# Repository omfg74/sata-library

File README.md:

# sata-library

Полка, в которой диски 3.5" лежат на местах. Ярус — четыре диска и высота 1U. Два яруса — 8 дисков, третий ставится теми же деталями. Одновременно под 12 В только одна сата-плата, и на ней моторы раскручиваются по одному.

Контроллер — ESP32. Он включает питание. Байты архива через ESP32 не идут: у него нет SATA, а USB слишком медленный для диска. Архив принимает Raspberry Pi 4 или мини-ПК и пишет его через покупные мосты USB–SATA командой `rsync`. Договор разъёмов — [hardware/INTERFACE.md](hardware/INTERFACE.md).

| что | чем открыть |
| --- | --- |
| схема и плата | KiCad 8, проекты в `hardware/controller` и `hardware/sata-board` |
| корпус | OpenSCAD, файлы в `cad/stack`. Картинка двух ярусов ниже |
| печать | PrusaSlicer, Cura или OrcaSlicer, STL из OpenSCAD |
| прошивка | VS Code с PlatformIO или Arduino IDE, каталог `hardware/controller/firmware` |

Платы заказывать нельзя. Зоны земли не залиты, DRC не прогнан, на сата-плате входной IRF4905 и стабилитрон D1 разведены неверно. Смотреть файлы: `flatpak run org.kicad.KiCad` (KiCad 10; файлы записаны как KiCad 8, сохранение поднимает формат). Футпринт XT60 на контроллере — заглушка, его подгоняют под разъём в руках.

Наборный ярус описан в [cad/stack/README.md](cad/stack/README.md). Порядок включения — в [docs/banks.md](docs/banks.md). Что ещё не закрыто без детали в руках — в [docs/open-questions.md](docs/open-questions.md).

Ниже отдельно лежит первая стойка на один юнит и примерка одного отсека. Наборный ярус их файлы не переписывает: `cad/rack.scad`, `cad/bay.scad`.

## С чего печатать ярус

```bash
make stl
```

Нужен OpenSCAD. В `cad/out/` появятся STL примерки и яруса. Ярус — файлы `stack-*.stl`.

PETG, сопло 0.4 мм, слой 0.2 мм, три стенки. Сколько каких деталей и какой длины трубки — в [cad/stack/README.md](cad/stack/README.md). Длинные пролёты не печатаются: это трубки 6 мм. Печатная деталь влезает в 170 мм.

## Софт

Хост включает слот и один диск, сверяет серийник и вызывает `rsync`. Паузу между раскрутками (`spin_pause_s`, в примере 8 с) держит хост. Сухой прогон на плату не выходит и `rsync` не запускает.

```bash
make test
PYTHONPATH=src python3 -m sata_library backup \
  --config config/library.example.toml --slot 1 --disk 1 --source /data --dry-run
```

В примере серийник `REPLACE-ME`, и сухой прогон подставляет его же. Это не чтение полки. Пока в манифесте пустая строка, копирование запрещено: сначала `identify`, потом серийник руками в TOML.

Живой контроллер:

```bash
PYTHONPATH=src python3 -m sata_library backup \
  --config config/library.toml --slot 1 --disk 1 --source /data --port /dev/ttyUSB0
```

Без `--port` команда останавливается с `not_connected`. Порт — 115200 8N1, строки из [docs/controller.md](docs/controller.md). `path_contains` на живом запуске обязателен. `mount` — уже смонтированный каталог диска, туда пишет `rsync -a`.

Диски разбираются из `lsblk -J`. У моста USB–SATA поле `tran` часто `usb`, поэтому полка фильтруется строкой `path_contains`, а не типом шины.

## Первая примерка и стойка 1U

Калибр и салазки — от варианта с подвижным разъёмом. Боевая полка их не использует.

`gauge.stl` — короткий ложемент, если снова мерить, где на корпусе сидит разъём. Диск кладётся к левому борту и на пол, задней плоскостью к нулю линеек. Окно в `sled.scad` сейчас по центру пластины и размером разъёма не является. Питание на эту примерку не подавать.

Каркас на один юнит — четыре уголка и восемь трубок, корзина на каждый диск.

`corner.stl` содержит левый и правый уголок. Печатать файл дважды. Гнездо 8.4 мм принимает трубку от 4 до 8 мм. В сборке по умолчанию трубка 6 мм: между верхней и нижней остаётся 29 мм, из них 1.6 мм пол корзины и 26.1 мм диск. Число корзин и диаметр задаются в `cad/params.scad`. Подробности в [docs/rack.md](docs/rack.md).

## Документы

- [docs/concept.md](docs/concept.md) — роли хоста и контроллера
- [docs/banks.md](docs/banks.md) — включение слота и одного диска
- [docs/controller.md](docs/controller.md) — текстовый протокол
- [docs/rack.md](docs/rack.md) — каркас 1U из уголков и трубок
- [docs/mechanics.md](docs/mechanics.md) — первая примерка подвижного разъёма
- [docs/hardware.md](docs/hardware.md) — из чего собрать: хост ARM, SATA или USB, питание и каркас
- [docs/open-questions.md](docs/open-questions.md) — что решить дальше
- [hardware/INTERFACE.md](hardware/INTERFACE.md) — разъёмы, питание, I2C

Лицензия MIT.

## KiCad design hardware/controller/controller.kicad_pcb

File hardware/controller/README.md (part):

# Плата контроллера полки

Плата включает 12 В на один слот и по I2C крутит диски на плате SATA. Байты архива через неё не идут: хост → USB 3.0 → покупной хаб → мост на плате SATA. На этой плате нет пар USB, пар SATA, W5500 и разъёма Ethernet.

Контроллер молчит, пока хост не пришлёт строку. Протокол — `hardware/INTERFACE.md`: `PING`, `ESTOP`, `STATE`, `SLOT n ON/OFF`, `DISK n d ON/OFF`, 115200 8N1. Паузу около 8 с между раскрутками дисков держит хост, в прошивке таймера на это нет.

## Открыть в KiCad

KiCad 8, бесплатный: https://www.kicad.org/

File → Open Project → `hardware/controller/controller.kicad_pro`.

Символы и футпринты лежат в `libs/` этого каталога (`sym-lib-table` и `fp-lib-table` смотрят на `${KIPRJMOD}`). Системная библиотека KiCad не нужна. Файлы собирает `python3 gen_board.py` из этого каталога; править плату лучше там и пересобрать.

## Что на плате

Вход XT60, ключ от переполюсовки IRF4905, предохранитель 10 А, всегда включённые 12 В. Модуль LM2596 (покупной, на гребёнке 1x4: VIN, GND, VOUT, GND) делает 5 В. AMS1117-3.3 делает 3,3 В для ESP32-WROOM-32E. Свой импульсный стабилизатор на плате не разведён.

Четыре одинаковых слота. На каждом полифуз 5 А и IRF4905 верхним ключом: исток на предохранителе, сток на клемму, затвор подтянут к истоку 100 кОм. Без прошивки слот выключен. 2N7002 тянет затвор к земле, когда GPIO высокий. Земля общая с USB и дисками, нижнего ключа нет.

Клемма 5,08 мм: контакт 1 — квадрат, шёлк «+», это +12V слота. Контакт 2 — шёлк «−», земля. К плате SATA — 18 AWG, короче 30 см, без диода в разрыв.

Гребёнка 2x5, шаг 2,54, вилка. Контакт 1 — квадрат и треугольник «1». Нумерация IDC: 1 и 2 в ряду торца, дальше по длинной стороне пары 3/4, 5/6, 7/8, 9/10. На плате торец (1, 2) ближе к верху, длинная сторона идёт вниз. Кабель прямой, контакт 1 к контакту 1, без переворота.

| Контакт | Сигнал |
| --- | --- |
| 1 | 3V3_AUX, всегда есть, не больше 50 мА |
| 2 | GND |
| 3 | PRESENT_N, плата SATA замыкает на землю |
| 4 | GND |
| 5 | SDA этого слота |
| 6 | SCL этого слота |
| 7 | GND |
| 8 | NC |
| 9 | NC |
| 10 | GND |

Подтяжек I2C на этих гребёнках нет: они стоят на плате SATA. На корневой шине, до мультиплексора, одна пара 4,7 кОм к 3,3 В.

TCA9548A, адрес 0x70 (A0 A1 A2 на земле). Канал 0 — слот 1, канал 3 — слот 4. SDA/SCL канала идут только на контакты 5 и 6 своей гребёнки. Сброс — GPIO13, активный низ, 10 кОм к 3,3 В.

PCF8574 на корневой шине, адрес 0x20, выводы никуда не идут. Это запас. Дисковый PCA9554 с тем же адресом 0x20 сидит за мультиплексором, на корне его нет.

ESP32-WROOM-32E антенной к верхней кромке. Под антенной медь не разведена, на обоих слоях зона запрета. GPIO слотов: 25, 26, 27, 14. PRESENT: 34, 35, 36, 39, с внешней подтяжкой 10 кОм к 3,3 В. I2C: GPIO21 SDA, GPIO22 SCL. Светодиод сердцебиения: GPIO32 через 1 кОм. EN и IO0 подтянуты к 3,3 В по 10 кОм, кнопки на землю.

Гребёнка UART 1x6, подпись UART: 3V3, GND, TX (GPIO1), RX (GPIO3), EN, IO0.

Плата ровно 100,0 × 100,0 мм, 1,6 мм, два слоя. Отверстия M3, сверло 3,2 мм: (4, 4), (96, 4), (4, 96), (96, 96). Клеммы слотов по нижнему краю, слева направо SLOT1…SLOT4, гребёнка сигнала рядом со своей клеммой. Корпуса TO-220 лежат плашмя, в дворе. Зоны земли на F.Cu и B.Cu нарисованы, но не залиты: в KiCad нажать B, потом DRC.

## BOM

Количества и футпринты — в `BOM.csv`. Ниже — что покупать и зачем.

| Кол-во | Деталь | Зачем |
| --- | --- | --- |
| 1 | ESP32-WROOM-32E | Модуль с антенной на плате. Голый кристалл и отдельная антенна тут не нужны. |
| 5 | IRF4905, TO-220 | P-канал, верхний ключ. Один на входе, четыре на слоты. Выводы 1=G, 2=D, 3=S. |
| 4 | 2N7002, SOT-23 | Тянет затвор IRF4905 к земле. Выводы этой разводки: 1=G, 2=S, 3=D. У части лотов порядок другой — сверить с даташитом пакета. |
| 1 | AMS1117-3.3, SOT-223 | 5 В → 3,3 В. Выводы 1=GND, 2=VOUT, 3=VIN, вкладка = VOUT. |
| 1 | TCA9548A, TSSOP-24 | Мультиплексор I2C, адрес 0x70. |
| 1 | PCF8574, SOIC-16 | Запас на корневой шине, адрес 0x20. Можно не паять. |
| 1 | Предохранитель 10 А, 5×20 мм, и держатель | После ключа переполюсовки. Шаг держателя на плате 22 мм — сверить с деталью. |
| 4 | Полифуз 2920, удержание около 5 А | На каждый слот, до силового ключа. |
| 4 | Клемма винтовая 2 контакта, шаг 5,08 мм | Питание слота. Низкий корпус, чтобы уложиться в 10 мм. |
| 4 | Вилка 2×5, шаг 2,54 мм | IDC к плате SATA. Контакт 1 — квадрат. |
| 1 | Модуль LM2596, 12 В → 5 В | Покупной. На плату выведена только гребёнка. Свой дроссель не разведён. |
| 1 | XT60, розетка на плату | Вход 12 В. Футпринт на плате — заглушка. |
| 1 | Стабилитрон 15 В, SOD-123 | Затвор-исток входного IRF4905. Катод (полоска, контакт 1) к истоку. |
| 1 | Адаптер USB-UART 3,3 В | Только для прошивки, на гребёнку UART. |

Остальное — 0805: 10 мкФ на входе и выходе AMS1117 и у ESP32, 100 нФ у ESP32 и у микросхем, 4,7 кОм на корневой I2C, 10 кОм на EN, IO0, сброс TCA и PRESENT, 100 кОм на затворах, 1 кОм на светодиод и на затворы 2N7002.

## Прошивка

Каталог `firmware/`. PlatformIO: плата `esp32dev`, framework Arduino, монитор 115200. Либо Arduino IDE, та же плата.

`pio run` из `firmware/` собирает образ для `esp32dev`. На плату его отсюда не заливали: ESP32 не был подключён. Правила слотов отдельно гоняются на хосте, без Arduino:

```
g++ -std=c++17 -Wall -Wextra -I firmware/src -o /tmp/policy_test firmware/policy_test.cpp firmware/src/policy.cpp && /tmp/policy_test
```

Правила «один слот», «DISK при выключенном слоте не меняет состояние», «ESTOP гасит всё», «n вне 1…4 — ошибка» лежат в `firmware/src/policy.cpp`, без Arduino.

Заливка, когда есть адаптер:

1. Адаптер USB-UART 3,3 В на гребёнку UART: 3V3, GND, TX адаптера на RX платы (GPIO3), RX адаптера на TX платы (GPIO1).
2. Зажать кнопку IO0 (или замкнуть IO0 на землю), нажать EN, отпустить IO0.
3. `pio run -t upload` из `firmware/`. Монитор — 115200. Плата сама ничего не печатает, пока не придёт строка.

Wi-Fi выключен, пока нет `firmware/include/secrets.h`. В репозитории только `secrets.h.example` с `WIFI_ENABLED 0`. Пароль в репозиторий не класть. Даже с Wi-Fi это те же короткие команды, порт 2323, без передачи архива.

Перед `SLOT n ON` прошивка смотрит PRESENT. Если нога высокая — `ERR not_present`, 12 В не включается. После включения ждёт до 300 мс и читает AT24C02 0x50 на канале `n-1`. Первые байты должны быть `S L I B`. Иначе слот снова гаснет: `ERR no_eeprom` или `ERR i2c`. PCA9554 0x20 на том же канале перед первым диском настраивается выходами в ноль: после питания он весь вход.

## Провод к одной плате SATA

Клемма: 18 AWG, плюс на контакт 1 (квадрат, «+»), минус на контакт 2 («−»). Короче 30 см. Диод в этот провод не ставить.

Шлейф IDC 2×5, прямой, контакт 1 к контакту 1. Треугольник на этой плате смотрит на тот же конец, что и квадрат на плате SATA. 3,3 В на контакте 1 — вспомогательное, его не коммутирует ключ слота. PRESENT_N плата SATA сажает на землю, когда она на месте.

Оранжевый провод 3,3 В питания SATA сюда не подключать. VBUS кабеля USB с хоста на эту плату не подавать: земля общая, питание 5 В дисков идёт своим путём на плате SATA.

## Перед заказом платы

- Футпринт XT60 — заглушка: площадки 5 мм, шаг 7,1 мм, шёлк «XT60 +12V» и «MATCH PART». Подогнать под ту розетку, которая в руках. На схеме та же заметка.
- Прижать IRF4905 к плате и измерить высоту. Бюджет корпуса — 10 мм. Плашмя корпус около 4,6 мм, но изогнутые выводы могут вылезти. Клеммы брать низкие. Модуль LM2596, если надеть его на гребёнку стоймя, в 10 мм не влезет: поставить рядом и припаять проводами.
- USB на эту плату не разводить. Данные — покупной хаб. На шелкографии так и написано.
- Шаг держателя предохранителя 5×20 сверить с деталью (на плате 22 мм).
- У 2N7002 сверить порядок ног с лотом: здесь 1=G, 2=S, 3=D.
- В KiCad нажать B, чтобы залить землю, затем Inspect → Design Rules Checker. Заливки в файле нет, DRC не запускался. KiCad 10 стоит через Flatpak, файлы записаны как KiCad 8, сохранение поднимает формат.

## Чего файл платы не гарантирует

DRC не запускался. Плату нельзя считать готовой к производству, пока зоны не залиты и DRC в KiCad не пройден. KiCad 10 стоит через Flatpak. Сохранение из него поднимает формат файлов с KiCad 8.

Дорожки 12 В слотов и вход до предохранителя — 2 мм. Возврат земли слота — 1,5 мм. Ветки затвора и стабилитрона — 0,4 мм, по ним не идёт ток слота. Переход 12 В с нижнего слоя на верхний — четыре отверстия сверлом 0,6 мм в ряд вдоль дорожки, шаг 1,6 мм. Площадки 1,2 мм лежат внутри дорожки 2 мм. Пара отверстий на пике 3–4 А яруса была на пределе, четыре делят тот же ток.

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
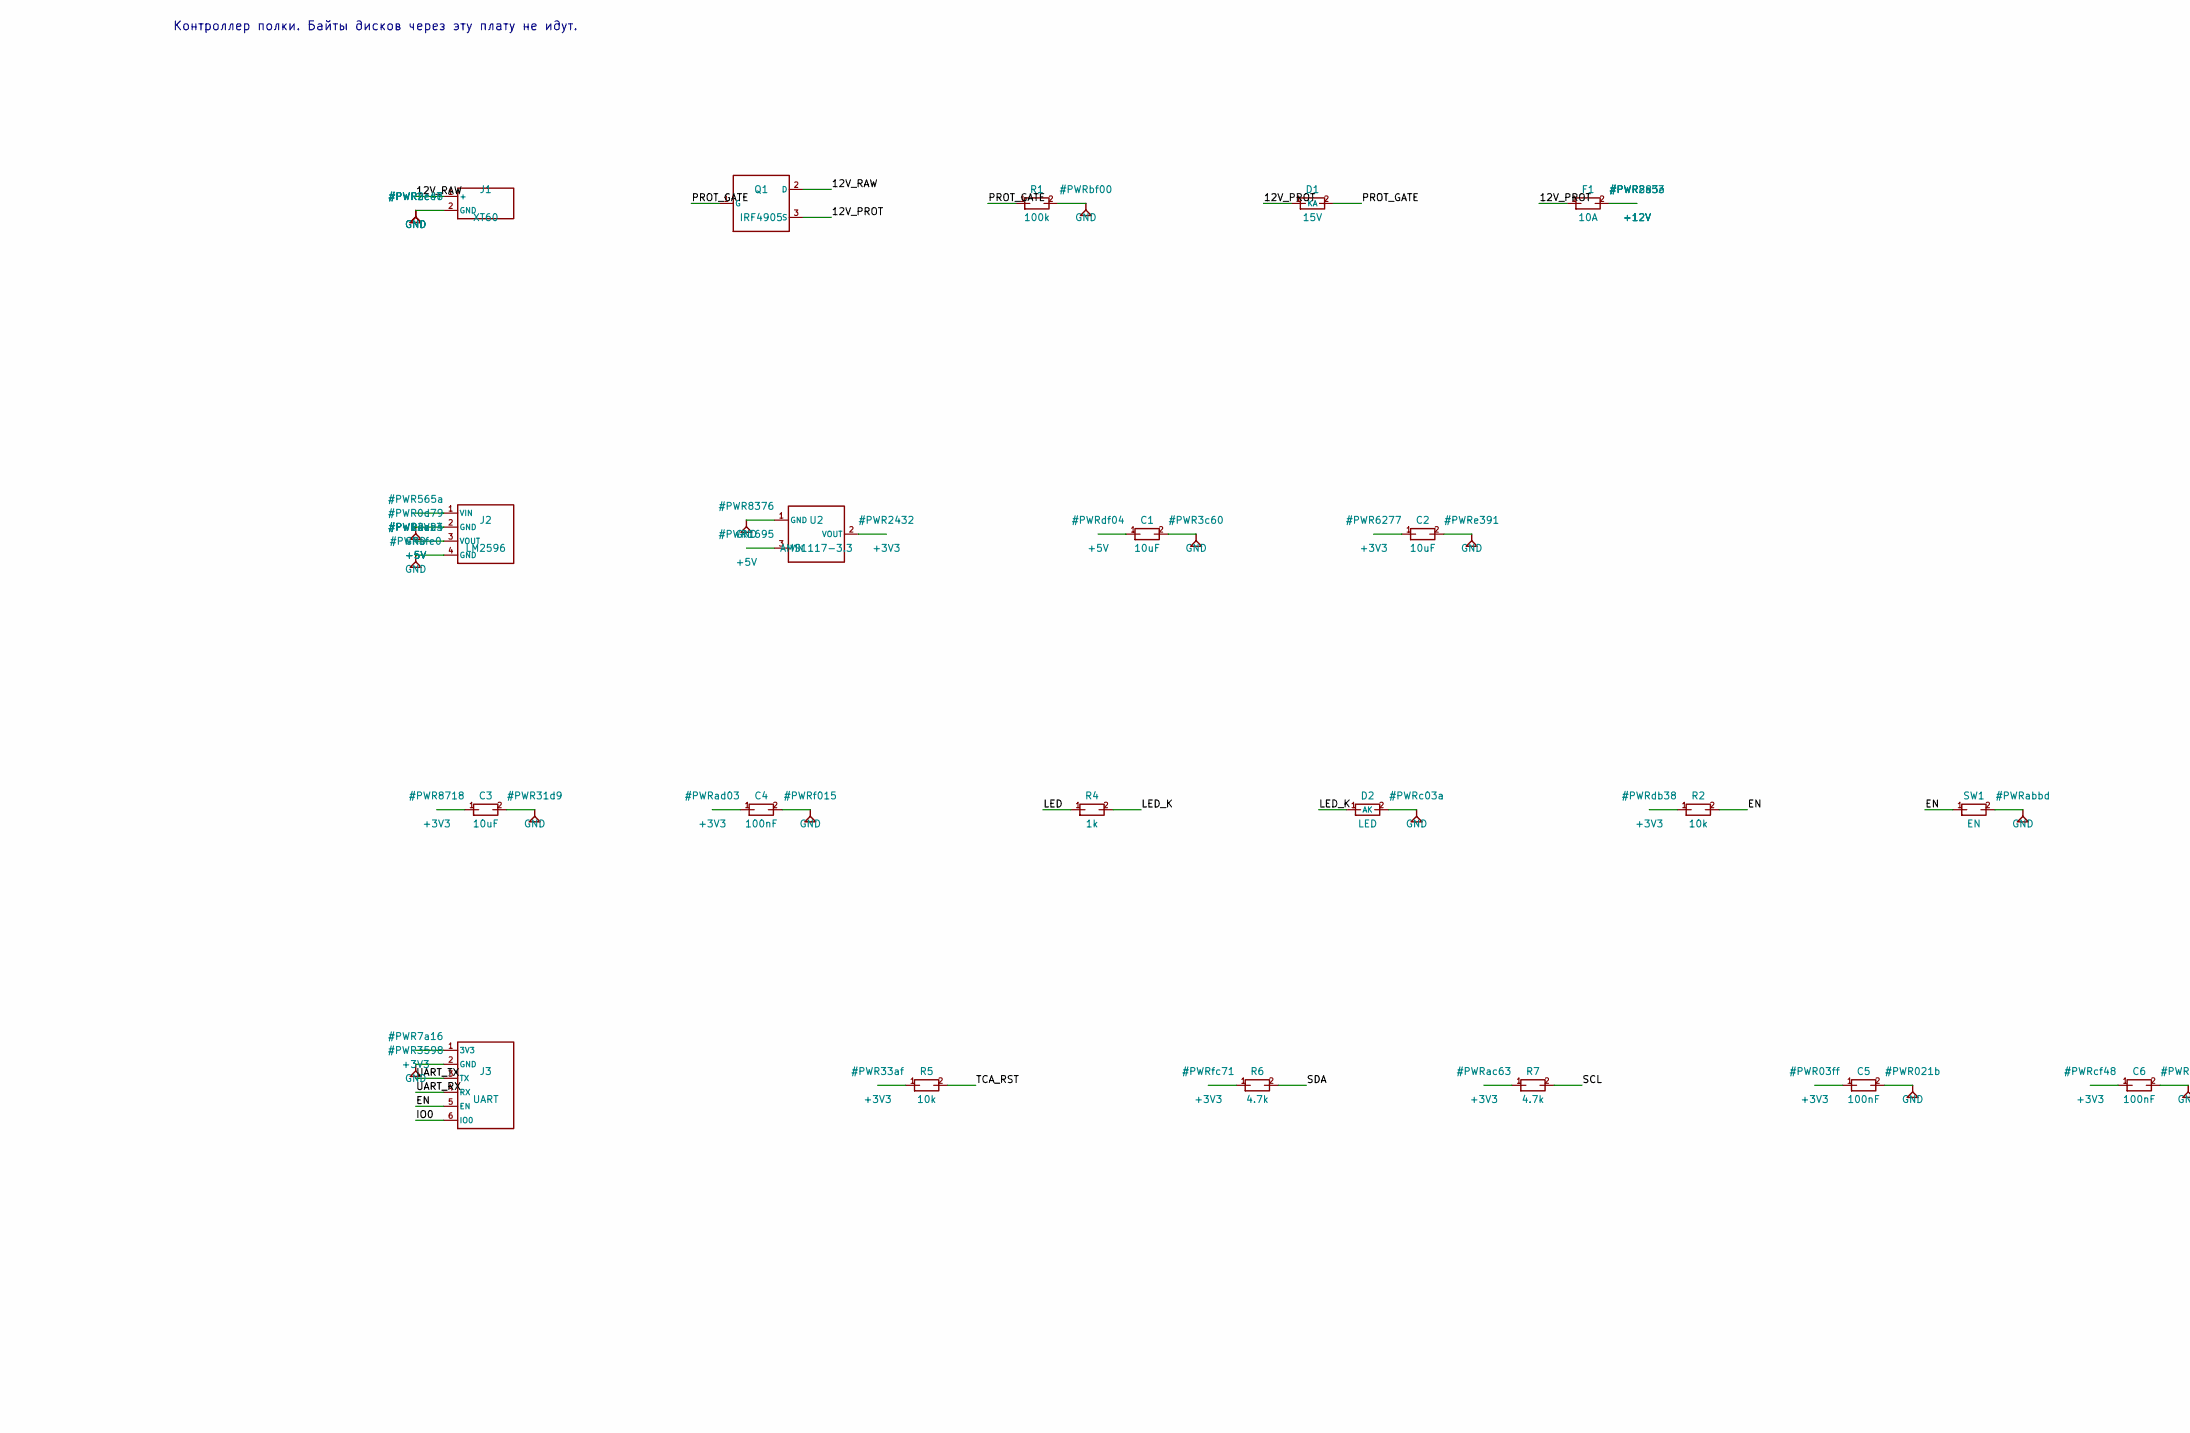
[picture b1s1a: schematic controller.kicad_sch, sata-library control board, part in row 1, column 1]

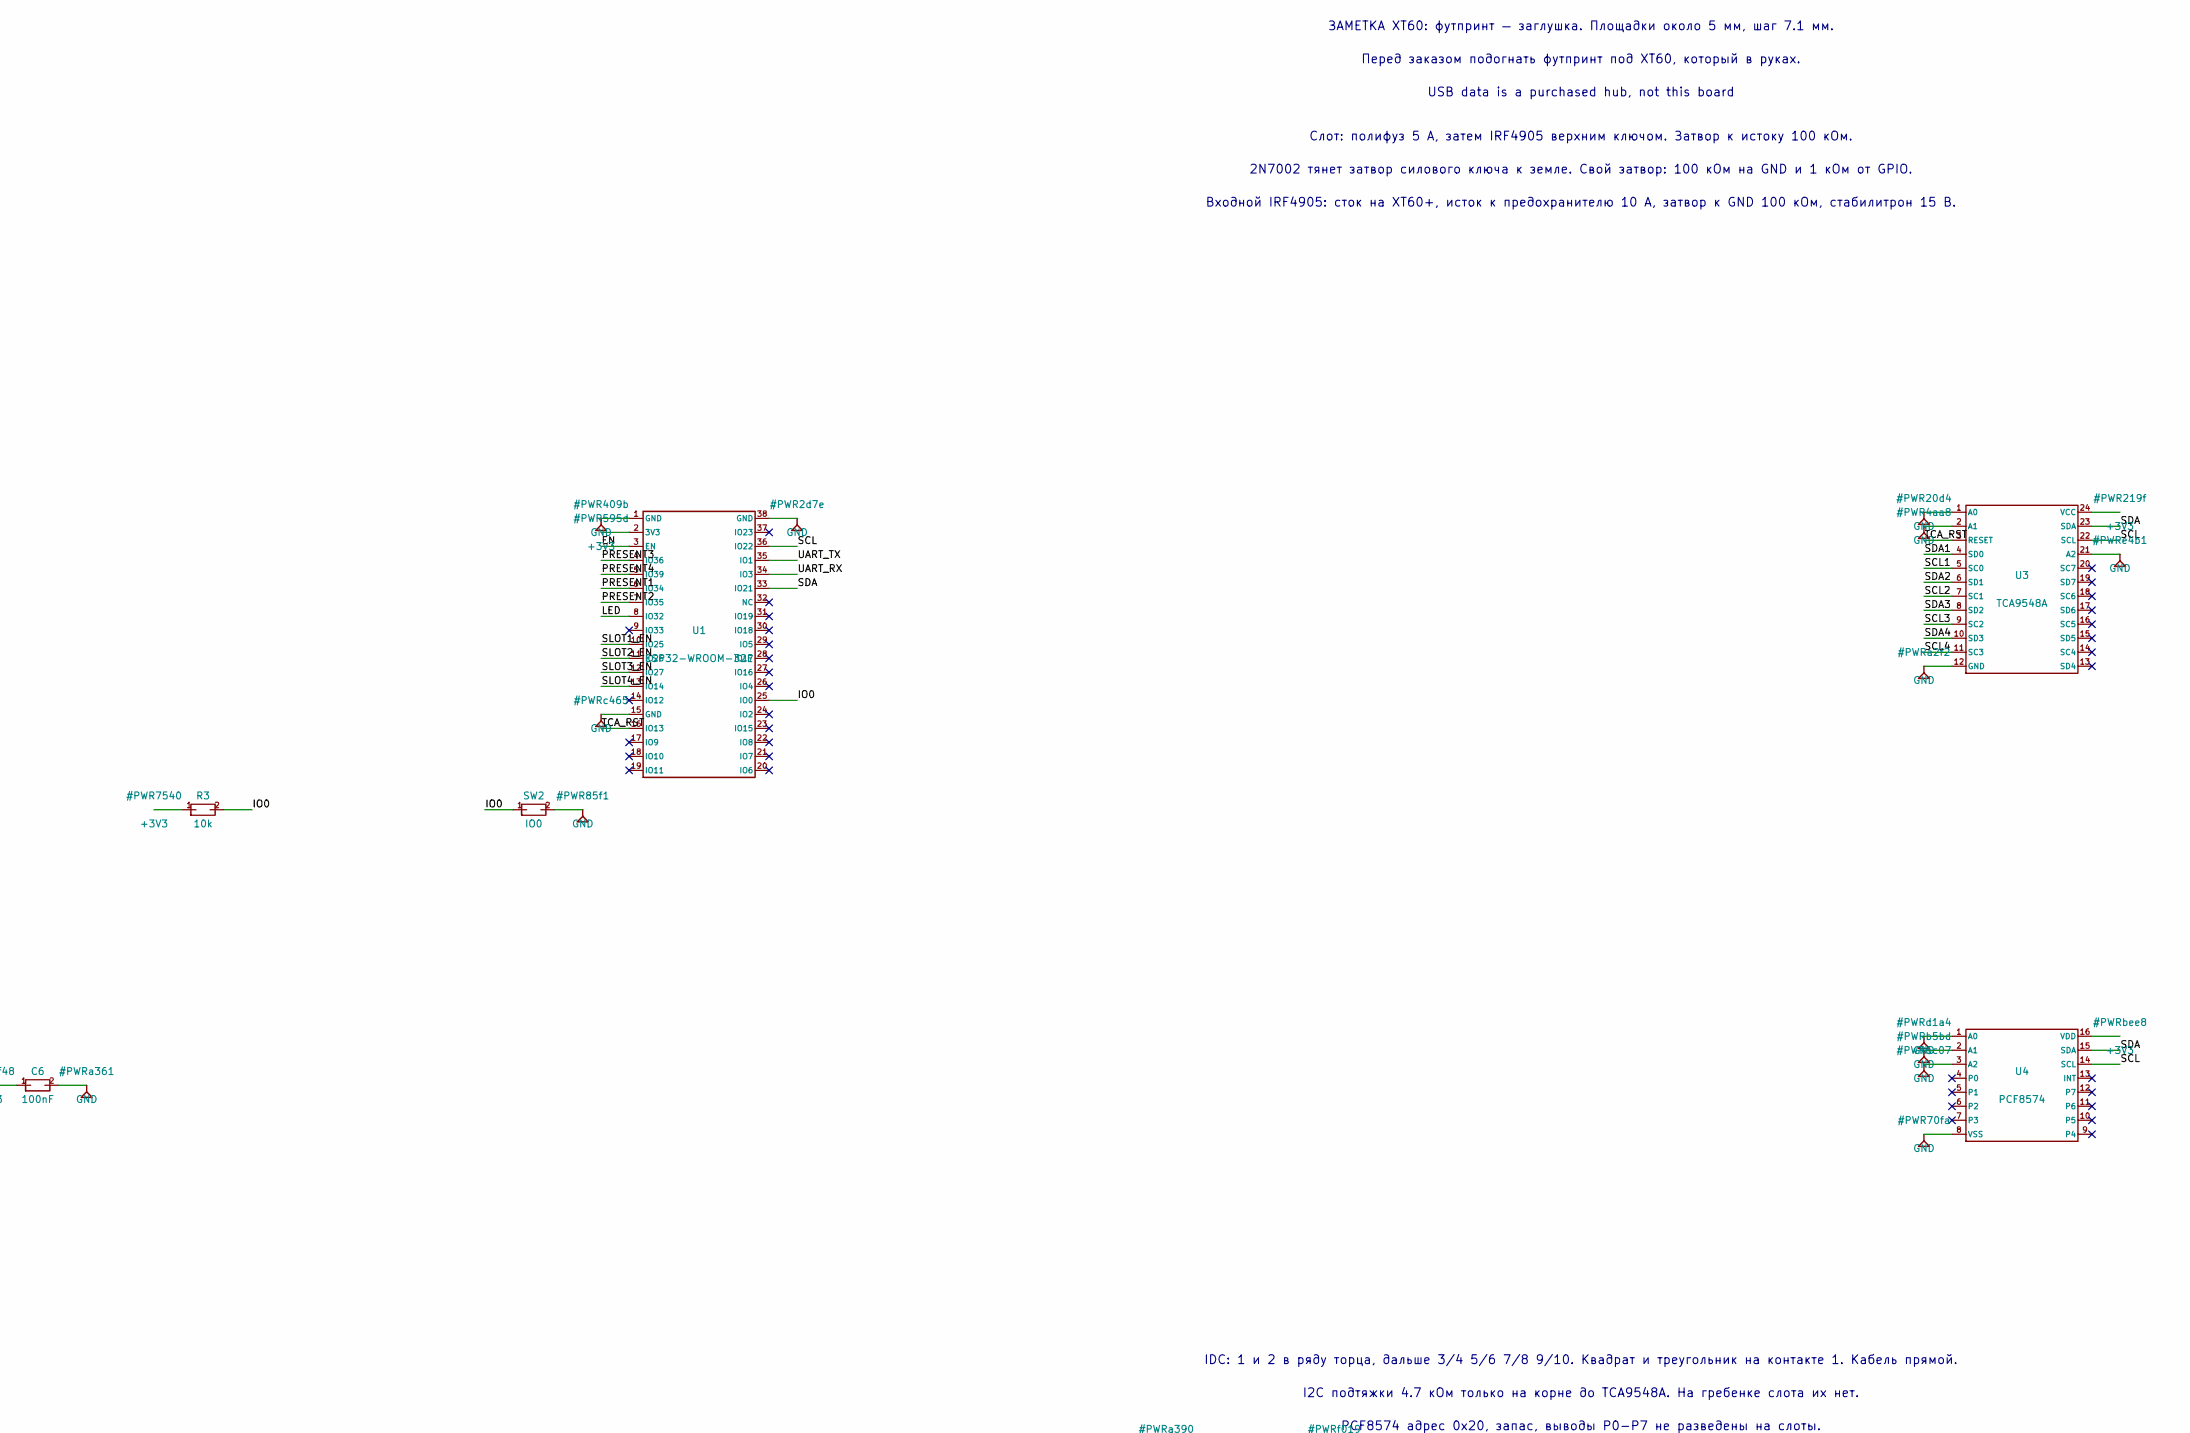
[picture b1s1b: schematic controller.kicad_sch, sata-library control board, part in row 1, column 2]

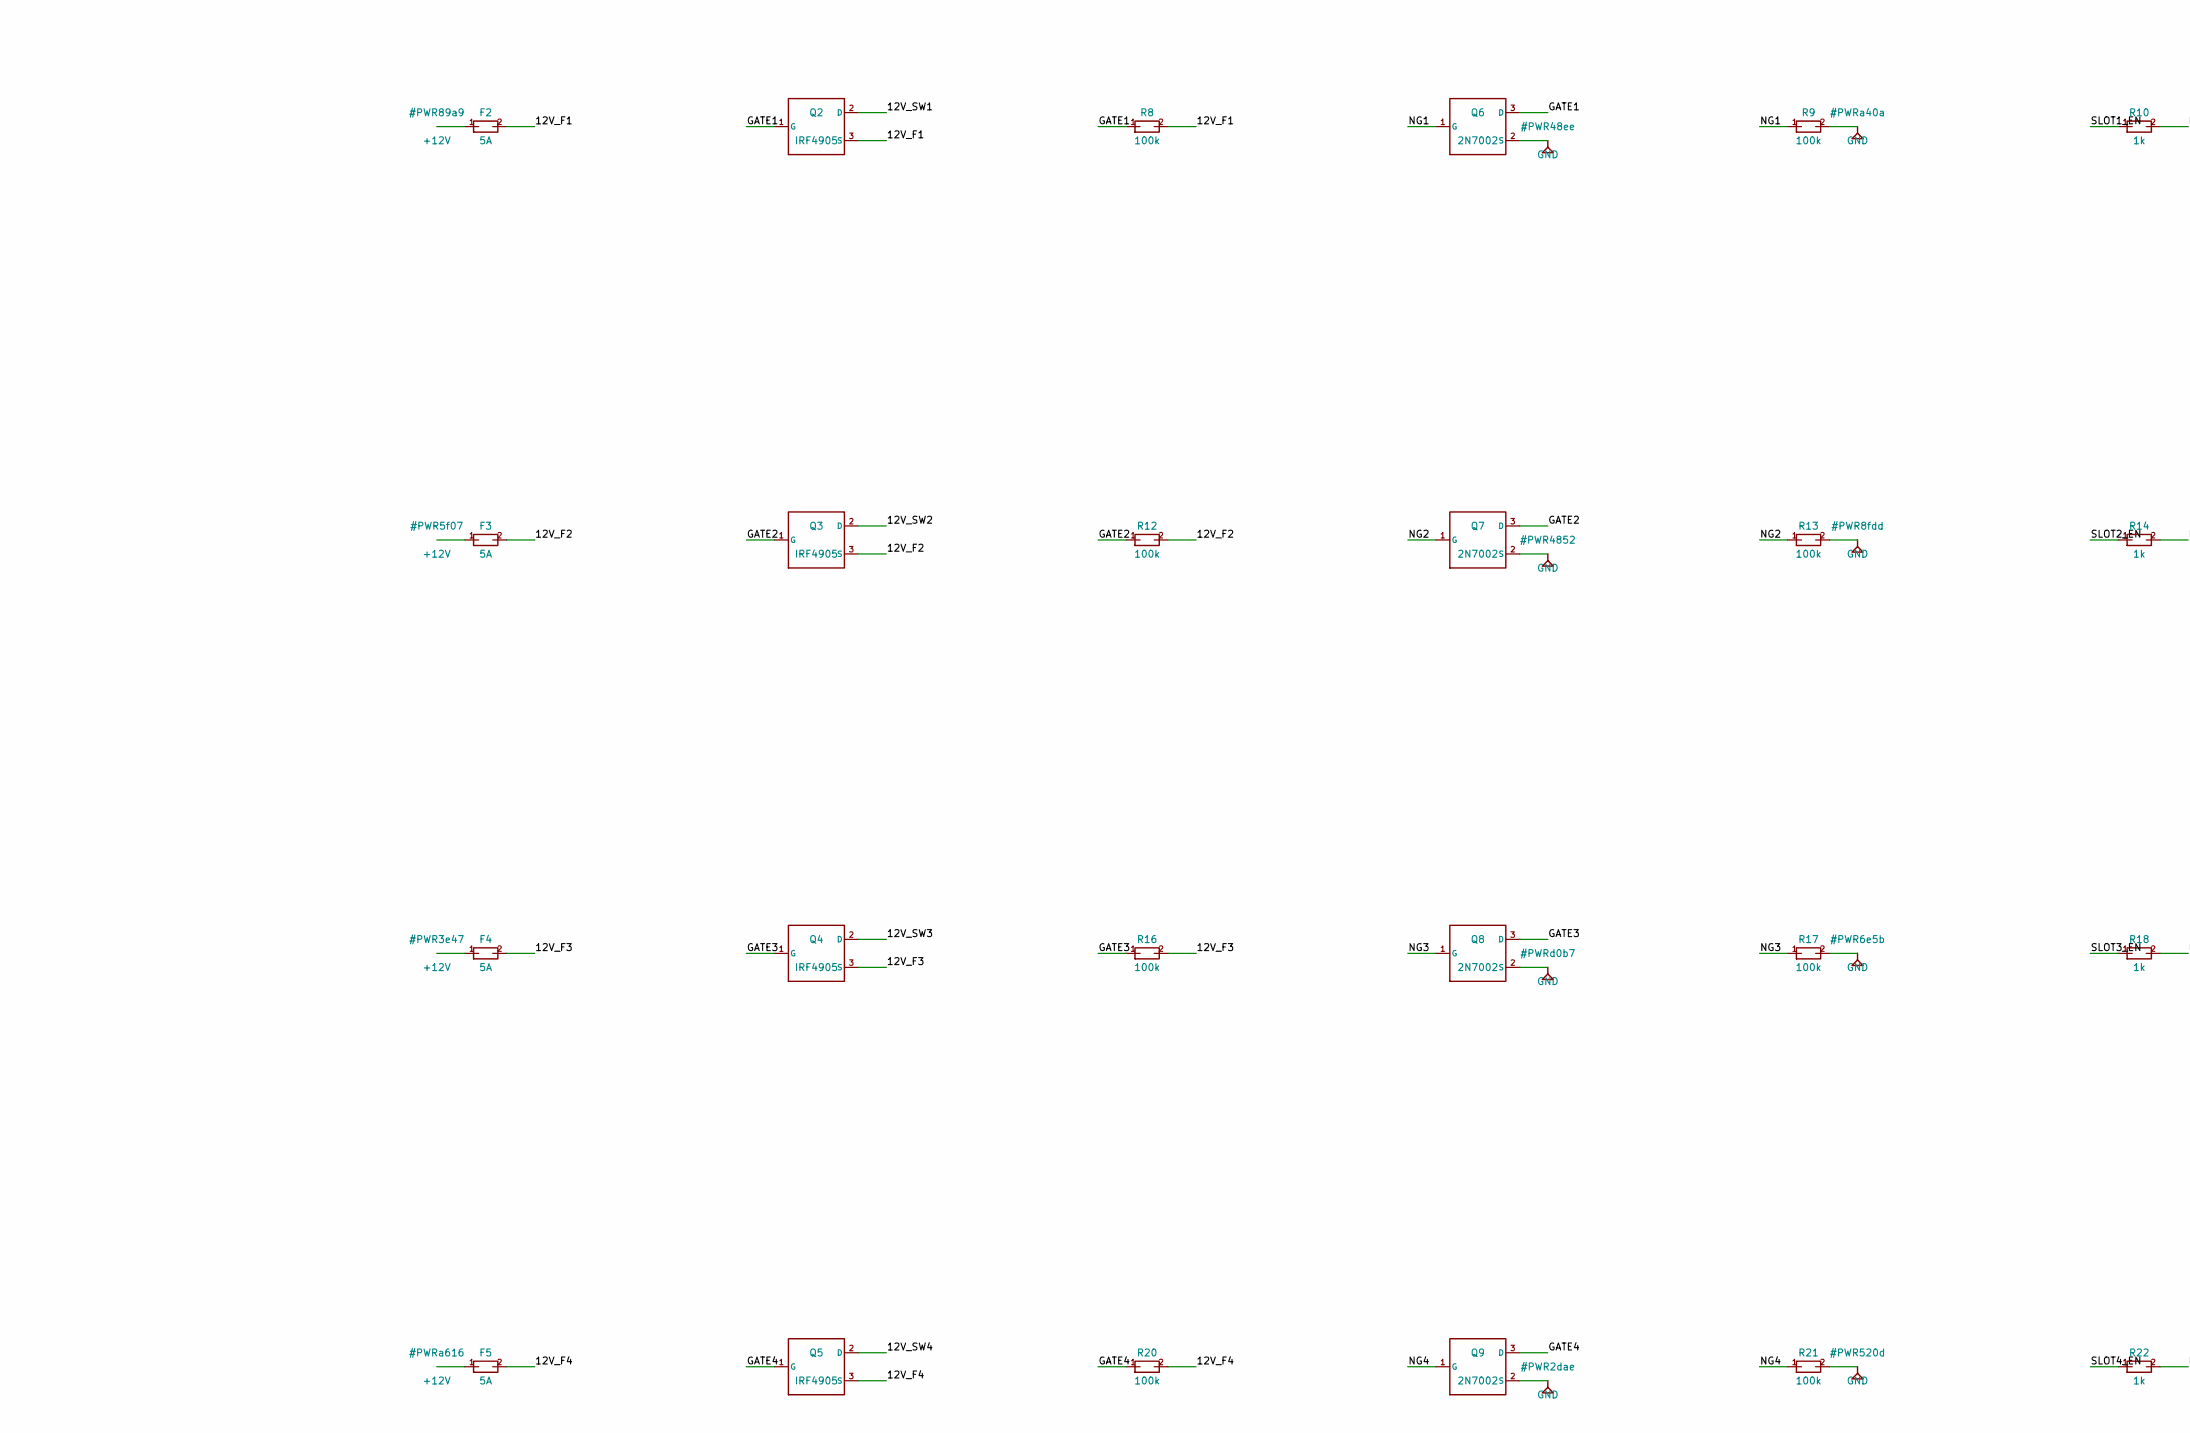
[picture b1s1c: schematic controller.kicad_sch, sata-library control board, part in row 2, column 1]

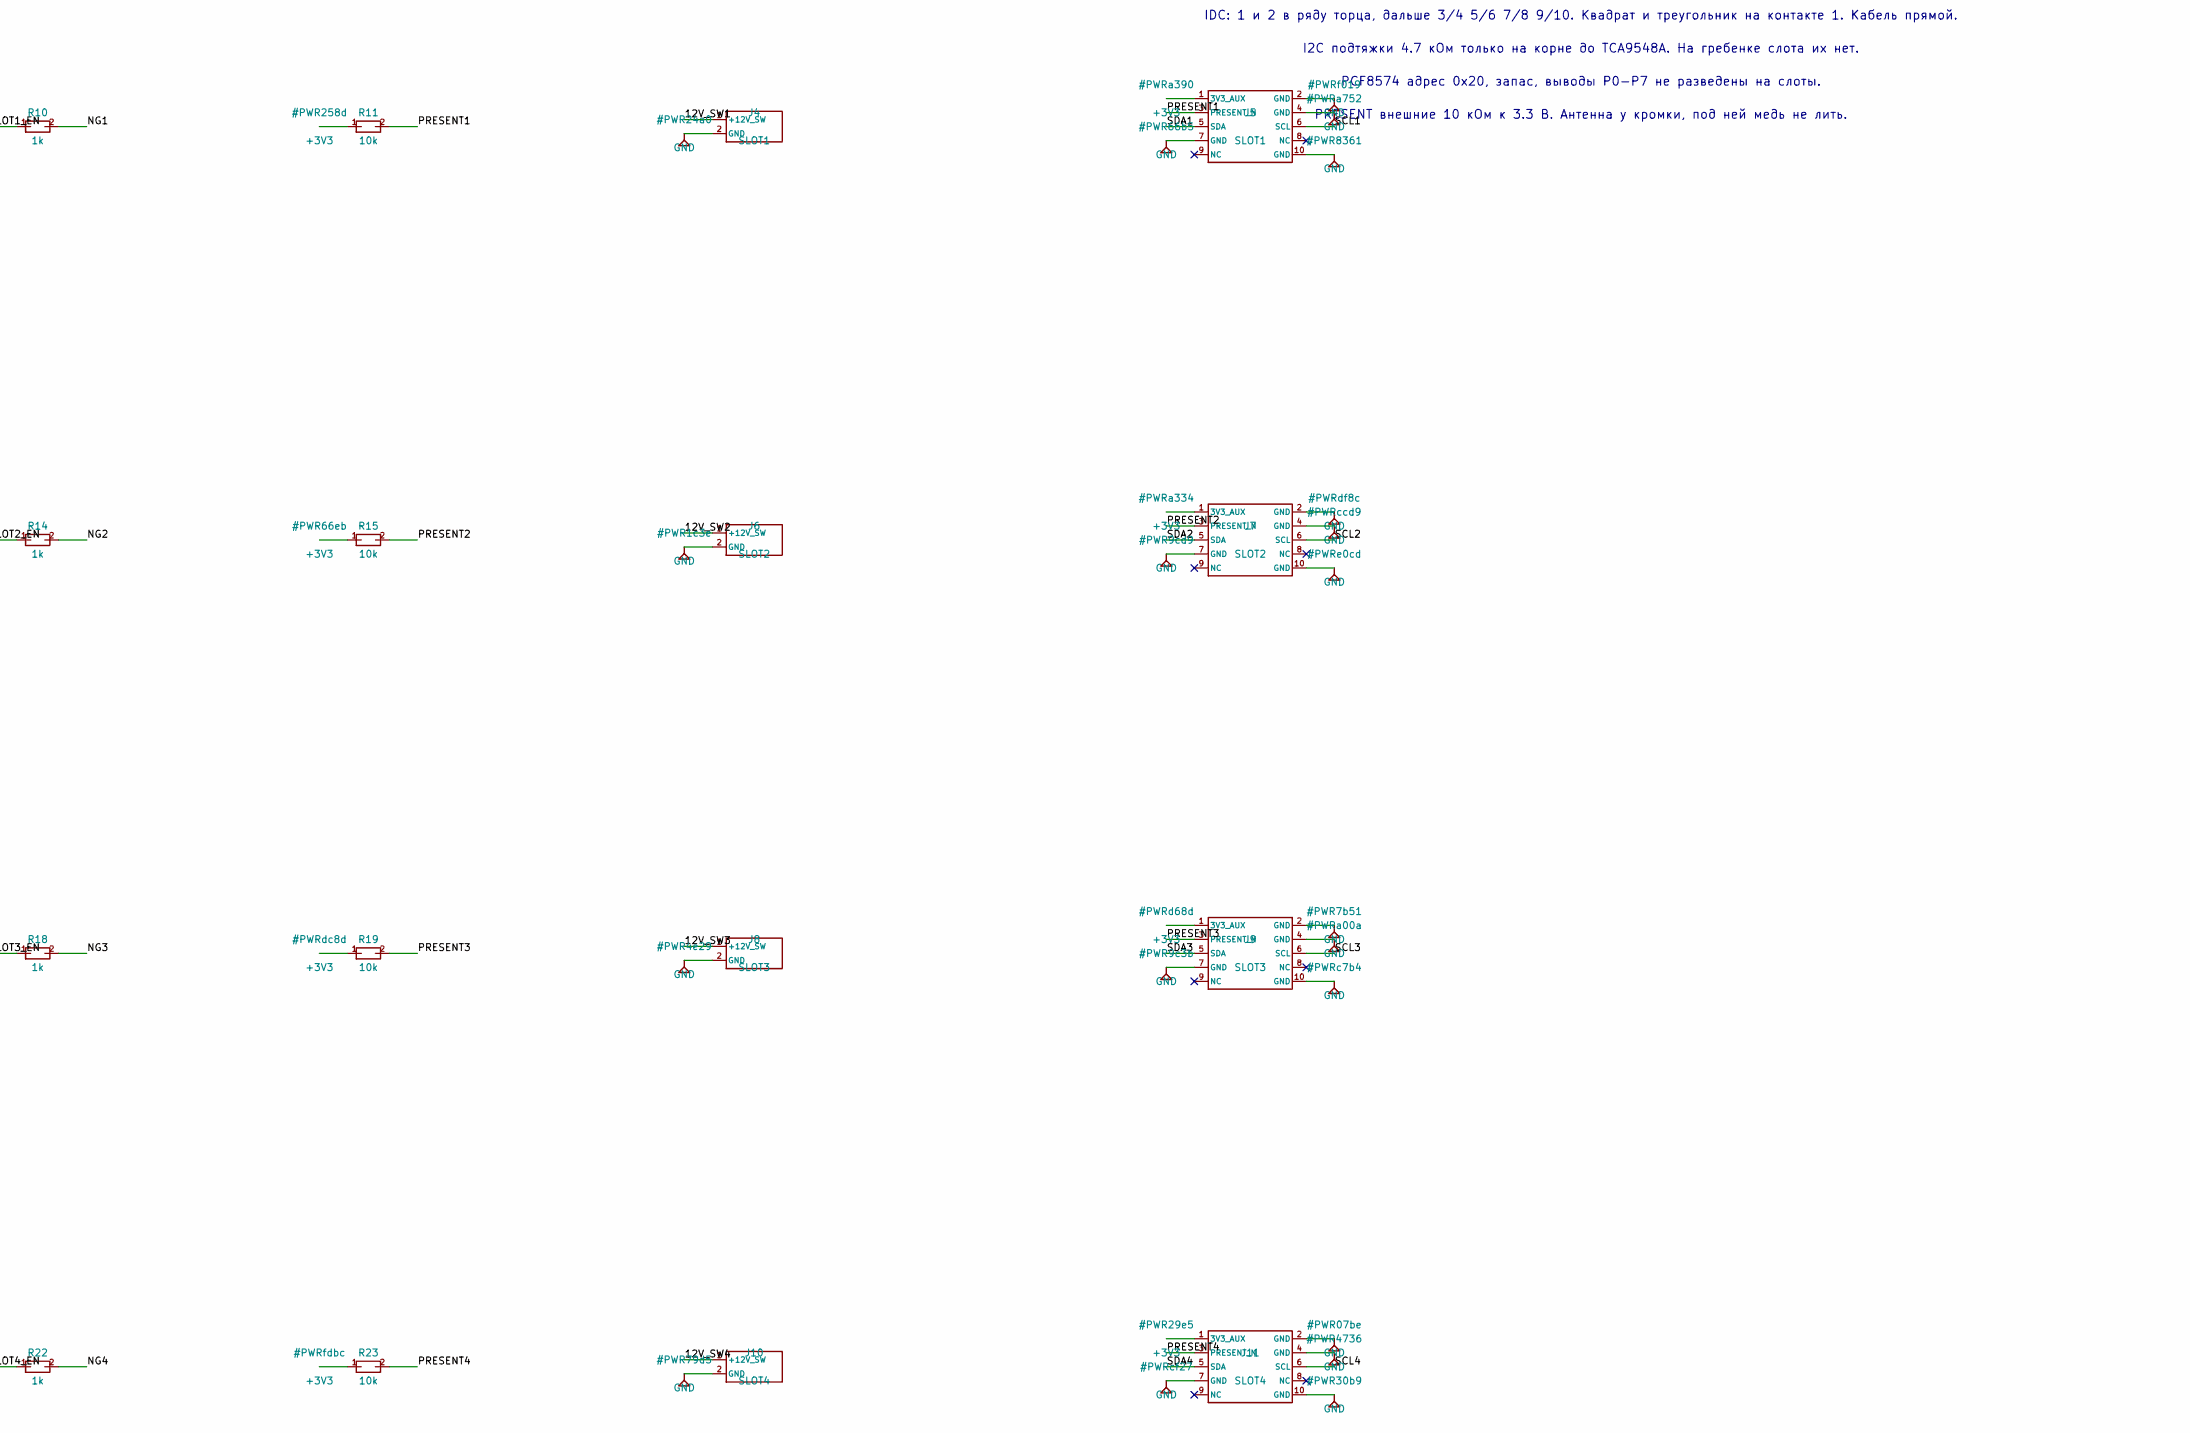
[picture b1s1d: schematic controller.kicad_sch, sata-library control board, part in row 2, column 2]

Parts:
C1, C2, C3: 10uF; C_0805
C4, C5, C6: 100nF; C_0805
D1: 15V; D_SOD-123
D2: LED; LED_0805
F1: 10A; Fuse_5x20
F2, F3, F4, F5: 5A; Polyfuse_2920
J1: XT60; XT60_Placeholder
J2: LM2596; PinHeader_1x04
J3: UART; PinHeader_1x06
J4: SLOT1; Terminal_2P_5.08
J5: SLOT1; PinHeader_2x05_IDC
J6: SLOT2; Terminal_2P_5.08
J7: SLOT2; PinHeader_2x05_IDC
J8: SLOT3; Terminal_2P_5.08
J9: SLOT3; PinHeader_2x05_IDC
J10: SLOT4; Terminal_2P_5.08
J11: SLOT4; PinHeader_2x05_IDC
Q1, Q2, Q3, Q4, Q5: IRF4905; TO-220-3_Flat
Q6, Q7, Q8, Q9: 2N7002; SOT-23
R1, R8, R9, R12, R13, R16, R17, R20, R21: 100k; R_0805
R2, R3, R5, R11, R15, R19, R23: 10k; R_0805
R4, R10, R14, R18, R22: 1k; R_0805
R6, R7: 4.7k; R_0805
SW1: EN; SW_Push_6mm
SW2: IO0; SW_Push_6mm
U1: ESP32-WROOM-32E
U2: AMS1117-3.3; SOT-223
U3: TCA9548A; TSSOP-24
U4: PCF8574; SOIC-16

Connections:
12V_F1: F2.2, Q2.3 (S), R8.2
12V_F2: F3.2, Q3.3 (S), R12.2
12V_F3: F4.2, Q4.3 (S), R16.2
12V_F4: F5.2, Q5.3 (S), R20.2
12V_PROT: D1.1 (K), F1.1, Q1.3 (S)
12V_RAW: J1.1 (+), Q1.2 (D)
12V_SW1: J4.1 (+12V_SW), Q2.2 (D)
12V_SW2: J6.1 (+12V_SW), Q3.2 (D)
12V_SW3: J8.1 (+12V_SW), Q4.2 (D)
12V_SW4: J10.1 (+12V_SW), Q5.2 (D)
+3V3: C2.1, C3.1, C4.1, C5.1, C6.1, J3.1 (3V3), J5.1 (3V3_AUX), J7.1 (3V3_AUX), J9.1 (3V3_AUX), J11.1 (3V3_AUX), R2.1, R3.1, R5.1, R6.1, R7.1, R11.1, R15.1, R19.1, R23.1, U1.2 (3V3), U2.2 (VOUT), U3.24 (VCC), U4.16 (VDD)
+5V: C1.1, J2.3 (VOUT), U2.3 (VIN)
+12V: F1.2, F2.1, F3.1, F4.1, F5.1, J2.1 (VIN)
EN: J3.5 (EN), R2.2, SW1.1, U1.3 (EN)
GATE1: Q2.1 (G), Q6.3 (D), R8.1
GATE2: Q3.1 (G), Q7.3 (D), R12.1
GATE3: Q4.1 (G), Q8.3 (D), R16.1
GATE4: Q5.1 (G), Q9.3 (D), R20.1
GND: C1.2, C2.2, C3.2, C4.2, C5.2, C6.2, D2.2 (K), J1.2 (GND), J2.2 (GND), J2.4 (GND), J3.2 (GND), J4.2 (GND), J5.2 (GND), J5.4 (GND), J5.7 (GND), J5.10 (GND), J6.2 (GND), J7.2 (GND), J7.4 (GND), J7.7 (GND), J7.10 (GND), J8.2 (GND), J9.2 (GND), J9.4 (GND), J9.7 (GND), J9.10 (GND), J10.2 (GND), J11.2 (GND), J11.4 (GND), J11.7 (GND), J11.10 (GND), Q6.2 (S), Q7.2 (S), Q8.2 (S), Q9.2 (S), R1.2, R9.2, R13.2, R17.2, R21.2, SW1.2, SW2.2, U1.1 (GND), U1.15 (GND), U1.38 (GND), U2.1 (GND), U3.1 (A0), U3.2 (A1), U3.12 (GND), U3.21 (A2), U4.1 (A0), U4.2 (A1), U4.3 (A2), U4.8 (VSS)
IO0: J3.6 (IO0), R3.2, SW2.1, U1.25 (IO0)
LED: R4.1, U1.8 (IO32)
LED_K: D2.1 (A), R4.2
NG1: Q6.1 (G), R9.1, R10.2
NG2: Q7.1 (G), R13.1, R14.2
NG3: Q8.1 (G), R17.1, R18.2
NG4: Q9.1 (G), R21.1, R22.2
PRESENT1: J5.3 (PRESENT_N), R11.2, U1.6 (IO34)
PRESENT2: J7.3 (PRESENT_N), R15.2, U1.7 (IO35)
PRESENT3: J9.3 (PRESENT_N), R19.2, U1.4 (IO36)
PRESENT4: J11.3 (PRESENT_N), R23.2, U1.5 (IO39)
PROT_GATE: D1.2 (A), Q1.1 (G), R1.1
SCL: R7.2, U1.36 (IO22), U3.22 (SCL), U4.14 (SCL)
SCL1: J5.6 (SCL), U3.5 (SC0)
SCL2: J7.6 (SCL), U3.7 (SC1)
SCL3: J9.6 (SCL), U3.9 (SC2)
SCL4: J11.6 (SCL), U3.11 (SC3)
SDA: R6.2, U1.33 (IO21), U3.23 (SDA), U4.15 (SDA)
SDA1: J5.5 (SDA), U3.4 (SD0)
SDA2: J7.5 (SDA), U3.6 (SD1)
SDA3: J9.5 (SDA), U3.8 (SD2)
SDA4: J11.5 (SDA), U3.10 (SD3)
SLOT1_EN: R10.1, U1.10 (IO25)
SLOT2_EN: R14.1, U1.11 (IO26)
SLOT3_EN: R18.1, U1.12 (IO27)
SLOT4_EN: R22.1, U1.13 (IO14)
TCA_RST: R5.2, U1.16 (IO13), U3.3 (RESET)
UART_RX: J3.4 (RX), U1.34 (IO3)
UART_TX: J3.3 (TX), U1.35 (IO1)

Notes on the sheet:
Контроллер полки. Байты дисков через эту плату не идут.
ЗАМЕТКА XT60: футпринт — заглушка. Площадки около 5 мм, шаг 7.1 мм.
Перед заказом подогнать футпринт под XT60, который в руках.
USB data is a purchased hub, not this board
Слот: полифуз 5 А, затем IRF4905 верхним ключом. Затвор к истоку 100 кОм.
2N7002 тянет затвор силового ключа к земле. Свой затвор: 100 кОм на GND и 1 кОм от GPIO.
Входной IRF4905: сток на XT60+, исток к предохранителю 10 А, затвор к GND 100 кОм, стабилитрон 15 В.
IDC: 1 и 2 в ряду торца, дальше 3/4 5/6 7/8 9/10. Квадрат и треугольник на контакте 1. Кабель прямой.
I2C подтяжки 4.7 кОм только на корне до TCA9548A. На гребенке слота их нет.
PCF8574 адрес 0x20, запас, выводы P0-P7 не разведены на слоты.
PRESENT внешние 10 кОм к 3.3 В. Антенна у кромки, под ней медь не лить.

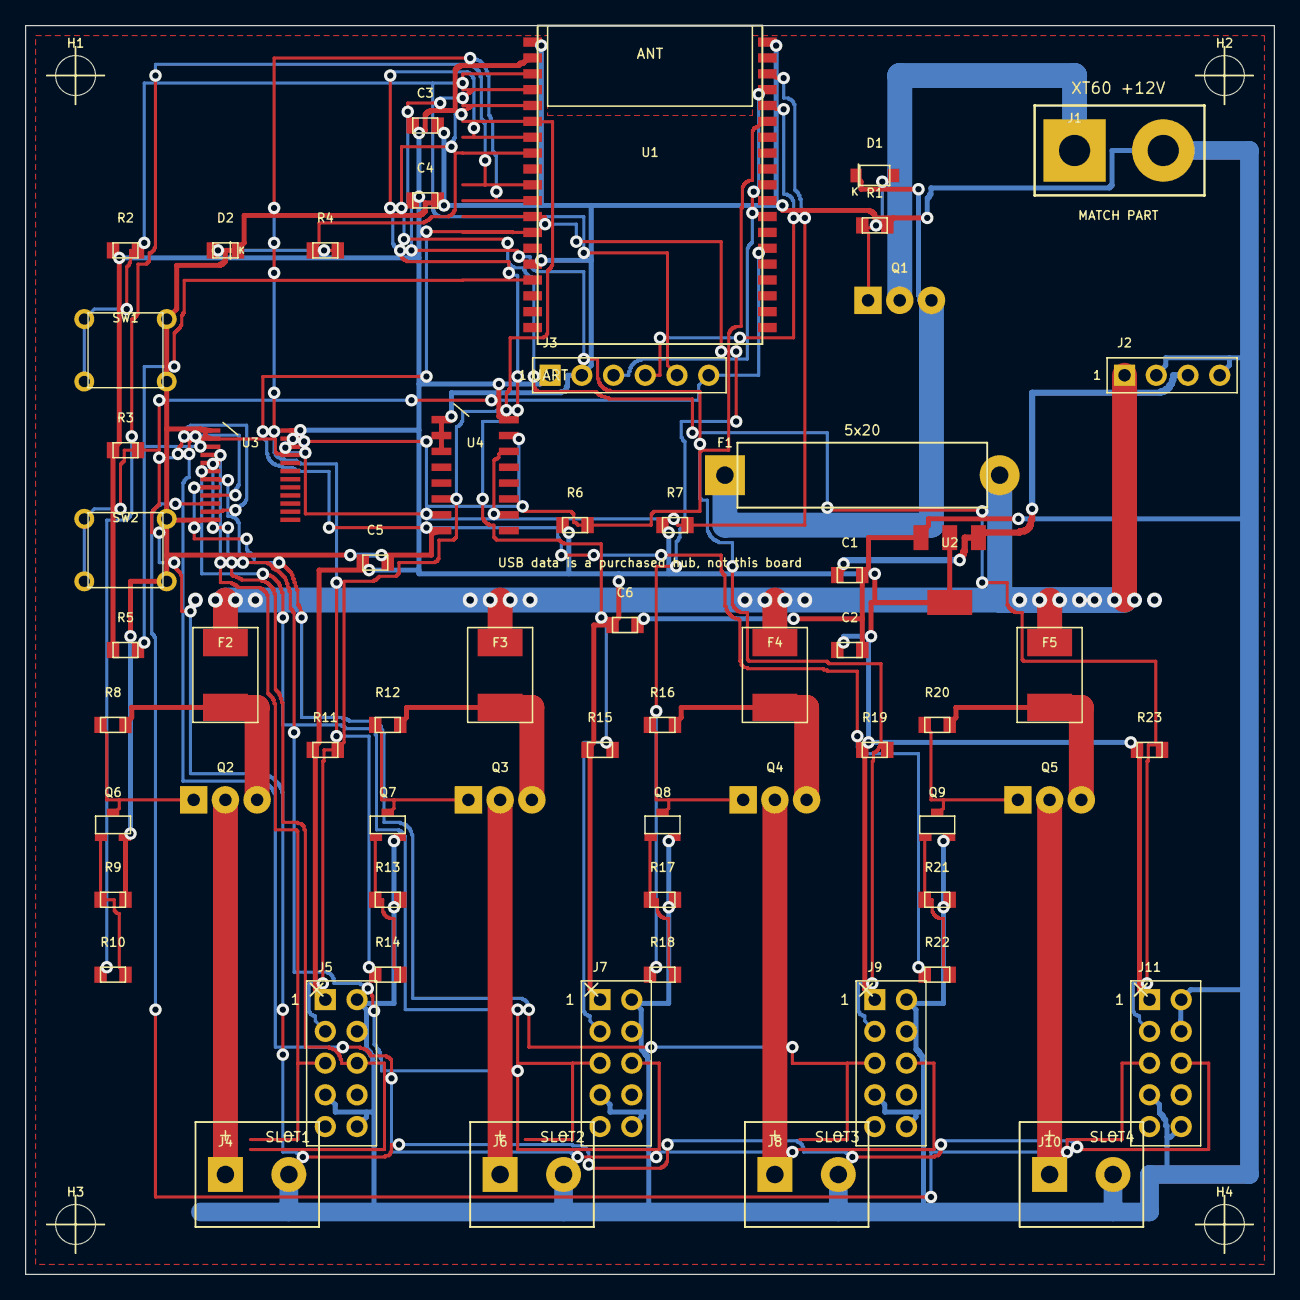
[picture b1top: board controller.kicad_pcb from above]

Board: 2 copper layers, 100.0 x 100.0 mm, 66 parts (0 on the bottom side), 48 nets.

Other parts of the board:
H1, H2, H3, H4: M3; MountingHole_3.2

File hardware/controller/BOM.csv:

ref,qty,value,footprint,notes
"J1",1,XT60,XT60_Placeholder,"заглушка: сверить площадки с деталью в руках"
"Q1 Q2 Q3 Q4 Q5",5,IRF4905,TO-220-3_Flat,"P-канал TO-220, 1=G 2=D 3=S, прижать к плате"
"R1 R8 R9 R12 R13 R16 R17 R20 R21",9,100k,R_0805,""
"D1",1,15V,D_SOD-123,"SOD-123, катод к истоку входного IRF4905"
"F1",1,10A,Fuse_5x20,"держатель 5x20, шаг 22 мм"
"J2",1,LM2596,PinHeader_1x04,"покупной модуль 12→5 В, на штыри VIN GND VOUT GND"
"U2",1,AMS1117-3.3,SOT-223,"SOT-223, 1=GND 2=VOUT 3=VIN, вкладка = VOUT"
"C1 C2 C3",3,10uF,C_0805,""
"C4 C5 C6",3,100nF,C_0805,""
"R4 R10 R14 R18 R22",5,1k,R_0805,""
"D2",1,LED,LED_0805,""
"R2 R3 R5 R11 R15 R19 R23",7,10k,R_0805,""
"SW1",1,EN,SW_Push_6mm,""
"SW2",1,IO0,SW_Push_6mm,""
"J3",1,UART,PinHeader_1x06,"гребёнка прошивки 1x6"
"R6 R7",2,4.7k,R_0805,""
"U1",1,ESP32-WROOM-32E,ESP32-WROOM-32E,"модуль с антенной на плате, антенный конец к кромке"
"U3",1,TCA9548A,TSSOP-24,"TSSOP-24, адрес 0x70, A0 A1 A2 на GND"
"U4",1,PCF8574,SOIC-16,"SOIC-16, адрес 0x20, запас, к слотам не подключён"
"F2 F3 F4 F5",4,5A,Polyfuse_2920,"полифуз 2920, удержание около 5 А"
"Q6 Q7 Q8 Q9",4,2N7002,SOT-23,"SOT-23, 1=G 2=S 3=D"
"J4",1,SLOT1,Terminal_2P_5.08,"клемма 5.08 мм 2 контакта, контакт 1 = +12V_SW, квадрат"
"J5",1,SLOT1,PinHeader_2x05_IDC,"вилка 2x5 IDC, контакт 1 квадрат и треугольник"
"J6",1,SLOT2,Terminal_2P_5.08,"клемма 5.08 мм 2 контакта, контакт 1 = +12V_SW, квадрат"
"J7",1,SLOT2,PinHeader_2x05_IDC,"вилка 2x5 IDC, контакт 1 квадрат и треугольник"
"J8",1,SLOT3,Terminal_2P_5.08,"клемма 5.08 мм 2 контакта, контакт 1 = +12V_SW, квадрат"
"J9",1,SLOT3,PinHeader_2x05_IDC,"вилка 2x5 IDC, контакт 1 квадрат и треугольник"
"J10",1,SLOT4,Terminal_2P_5.08,"клемма 5.08 мм 2 контакта, контакт 1 = +12V_SW, квадрат"
"J11",1,SLOT4,PinHeader_2x05_IDC,"вилка 2x5 IDC, контакт 1 квадрат и треугольник"
"H1 H2 H3 H4",4,M3,MountingHole_3.2,"сверло 3.2 мм, центры (4,4) (96,4) (4,96) (96,96)"
